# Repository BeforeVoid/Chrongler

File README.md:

# Chrongler

eurorack open-source module based on forestcover Benjolin with few mods.
+ Rungler clock input.
+ Band Pass output.
+ High Pass output.

Strictly for non-commercial use.

CC-By-NC 4.0, 2026.

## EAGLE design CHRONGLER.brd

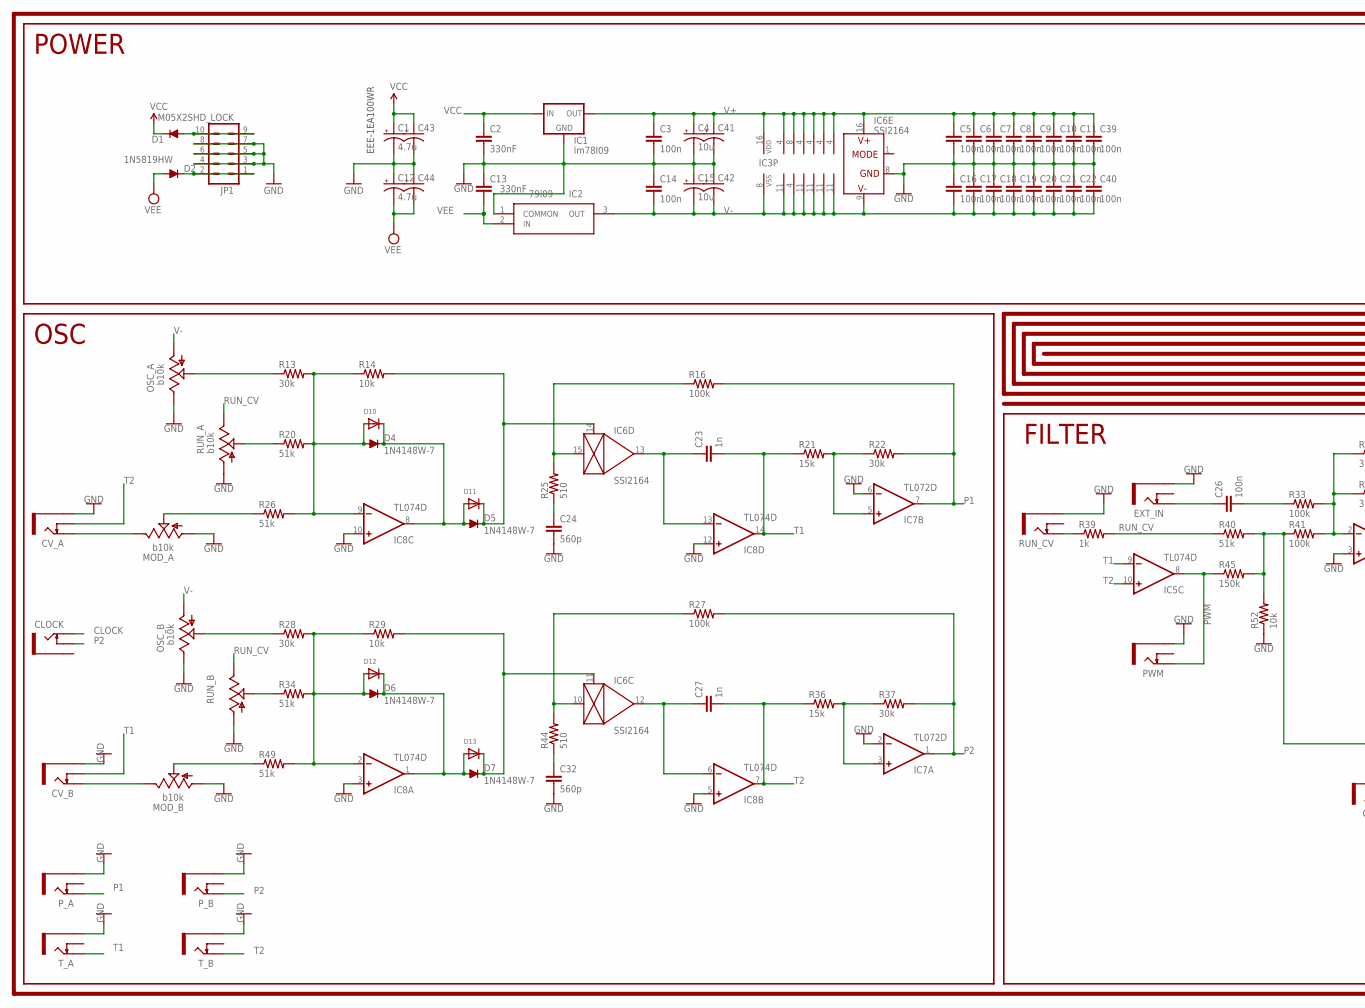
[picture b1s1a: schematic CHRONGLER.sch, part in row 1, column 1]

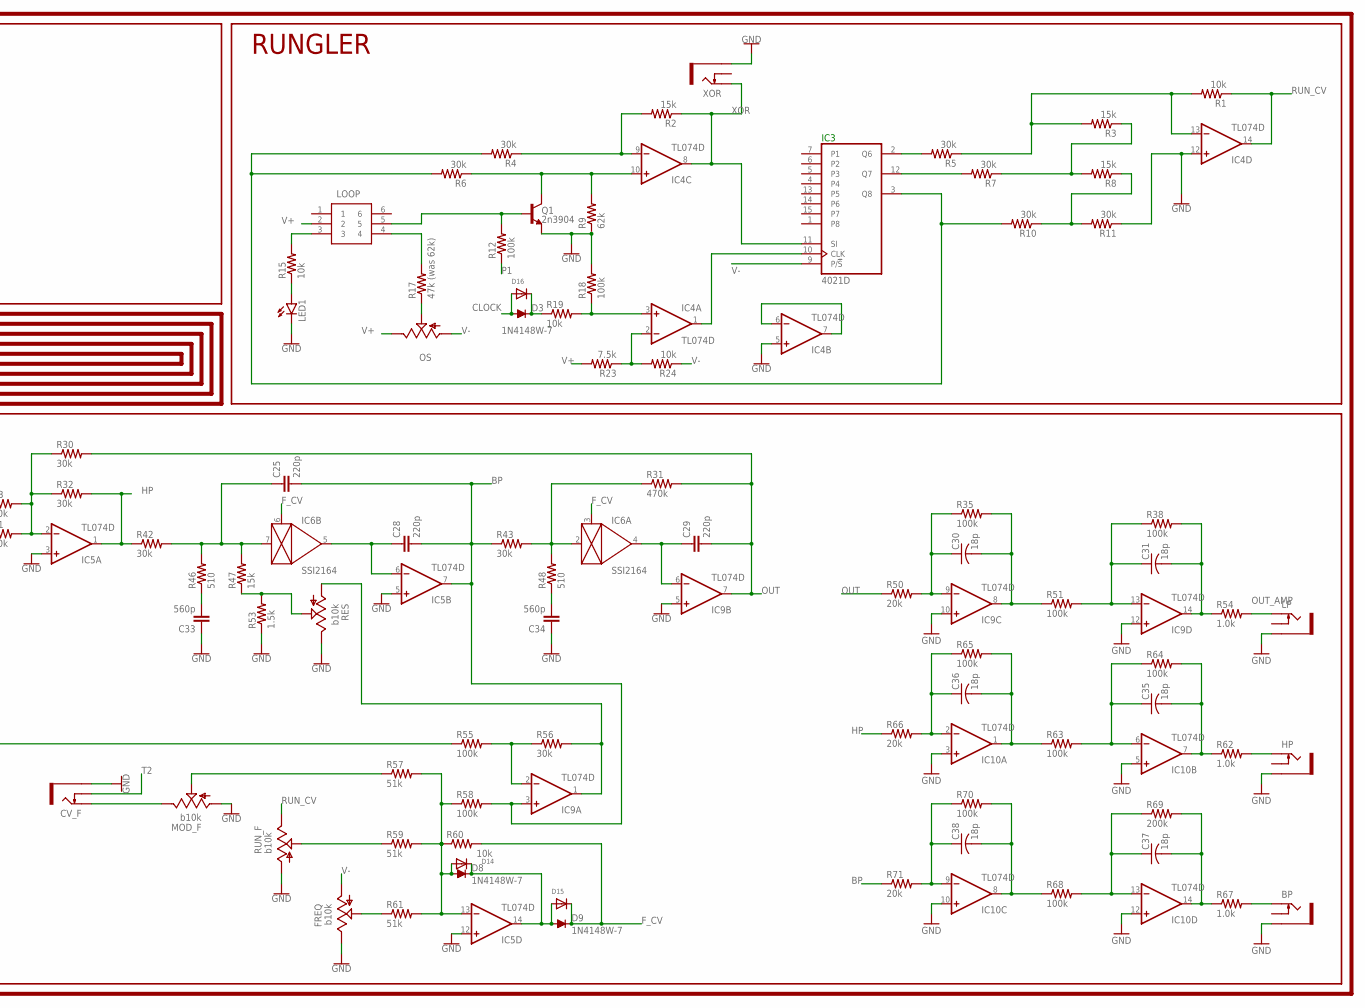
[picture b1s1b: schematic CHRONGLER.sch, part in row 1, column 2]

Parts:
BP: THONKICONNNEW; WQP-PJ301M-12_JACK
C1, C12: 4.7u; PANASONIC_C
C2, C13: 330nF; C1206
C3, C14: 100n; C1206
C4, C15: 10u; PANASONIC_C
C5, C6, C7, C8, C9, C10, C11, C16, C17, C18, C19, C20, C21, C22, C26, C39, C40: 100n; C0603
C23, C27: 1n; C0603
C24, C32, C33, C34: 560p; C0603
C25, C28, C29: 220p; C0603
C30, C31, C35, C36, C37, C38: 18p; C0603
C41, C42, C43, C44: CPOL-USE2.5-6; E2,5-6
CLOCK: THONKICONNNEW; WQP-PJ301M-12_JACK
CV_A: THONKICONNNEW; WQP-PJ301M-12_JACK
CV_B: THONKICONNNEW; WQP-PJ301M-12_JACK
CV_F: THONKICONNNEW; WQP-PJ301M-12_JACK
D1, D2: 1N5819HW; SOD123
D3, D4, D5, D6, D7, D8, D9: 1N4148W-7; SOD123
D10, D11, D12, D13, D14, D15, D16: DIODESOD-323F; SOD-323F
EXT_IN: THONKICONNNEW; WQP-PJ301M-12_JACK
FREQ: b10k; 9MM_SNAP-IN_POT
HP: THONKICONNNEW; WQP-PJ301M-12_JACK
IC1: lm78l09; SOT89
IC2: 79l09; SOT-89-3
IC3: 4021D; SO16
IC4, IC5, IC8, IC9, IC10: TL074D; SO14
IC6: SSI2164; SOIC16N
IC7: TL072D; SO08
JP1: M05X2SHD_LOCK; 2X5-SHROUDED_LOCK
LED1: LEDLD260; LD260
LOOP: MHPS2266; DIPS450W80P200L600H1050Q6N
LP: THONKICONNNEW; WQP-PJ301M-12_JACK
MOD_A: b10k; 9MM_SNAP-IN_POT
MOD_B: b10k; 9MM_SNAP-IN_POT
MOD_F: b10k; 9MM_SNAP-IN_POT
OS: 9MM_SNAP-IN_POT_; 9MM_SNAP-IN_POT
OSC_A: b10k; 9MM_SNAP-IN_POT
OSC_B: b10k; 9MM_SNAP-IN_POT
PWM: THONKICONNNEW; WQP-PJ301M-12_JACK
P_A: THONKICONNNEW; WQP-PJ301M-12_JACK
P_B: THONKICONNNEW; WQP-PJ301M-12_JACK
Q1: 2n3904; SOT23-3
R1, R14, R15, R19, R24, R29, R52, R60: 10k; R0603
R2, R3, R8, R21, R36, R47: 15k; R0603
R4, R5, R6, R7, R10, R11, R13, R22, R28, R30, R32, R37, R42, R43, R56: 30k; R0603
R9: 62k; R0603
R12, R16, R18, R27, R33, R35, R38, R41, R51, R55, R58, R63, R64, R65, R68, R70: 100k; R0603
R17: 47k (was 62k); R0603
R20, R26, R34, R40, R49, R57, R59, R61: 51k; R0603
R23: 7.5k; R0603
R25, R44, R46, R48: 510; R0603
R31: 470k; R0603
R39: 1k; R0603
R45: 150k; R0603
R50, R66, R71: 20k; R0603
R53: 1.5k; R0603
R54, R62, R67: 1.0k; R0603
R69: 200k; R0603
RES: b10k; 9MM_SNAP-IN_POT
RUN_A: b10k; 9MM_SNAP-IN_POT
RUN_B: 9MM_SNAP-IN_POT_; 9MM_SNAP-IN_POT
RUN_CV: THONKICONNNEW; WQP-PJ301M-12_JACK
RUN_F: b10k; 9MM_SNAP-IN_POT
T_A: THONKICONNNEW; WQP-PJ301M-12_JACK
T_B: THONKICONNNEW; WQP-PJ301M-12_JACK
XOR: THONKICONNNEW; WQP-PJ301M-12_JACK

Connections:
BP: C25.2, C28.2, IC5.7 (OUT), IC9.3 (+IN), R43.1, R58.2, R71.1
CLOCK: CLOCK.P$1_TIP (TIP), D3.A, D16.A
F_CV: D9.C, D15.C, IC6.3 (CTRL), IC6.6 (CTRL), R60.2
GND: BP.P$3_SLEEVE (SLEEVE), C1.-, C2.2, C3.2, C4.-, C5.2, C6.2, C7.2, C8.2, C9.2, C10.2, C11.2, C12.+, C13.1, C14.1, C15.+, C16.1, C17.1, C18.1, C19.1, C20.1, C21.1, C22.1, C24.2, C32.2, C33.1, C34.1, C39.2, C40.1, C41.-, C42.+, C43.-, C44.+, CV_A.P$3_SLEEVE (SLEEVE), CV_B.P$3_SLEEVE (SLEEVE), CV_F.P$3_SLEEVE (SLEEVE), EXT_IN.P$3_SLEEVE (SLEEVE), FREQ.3 (E), HP.P$3_SLEEVE (SLEEVE), IC1.2 (GND), IC1.2@1 (GND), IC2.1 (COMMON), IC4.5 (+IN), IC4.12 (+IN), IC5.3 (+IN), IC5.5 (+IN), IC5.12 (+IN), IC6.8 (GND), IC7.2 (-IN), IC7.6 (-IN), IC8.3 (+IN), IC8.5 (+IN), IC8.10 (+IN), IC8.12 (+IN), IC9.5 (+IN), IC9.10 (+IN), IC9.12 (+IN), IC10.3 (+IN), IC10.5 (+IN), IC10.10 (+IN), IC10.12 (+IN), JP1.3, JP1.4, JP1.5, JP1.6, JP1.7, JP1.8, LED1.K (C), LP.P$3_SLEEVE (SLEEVE), MOD_A.1 (A), MOD_B.1 (A), MOD_F.1 (A), OSC_A.3 (E), OSC_B.3 (E), PWM.P$3_SLEEVE (SLEEVE), P_A.P$3_SLEEVE (SLEEVE), P_B.P$3_SLEEVE (SLEEVE), Q1.2 (E), R9.1, R11.1, R18.2, R52.1, R53.1, RES.3 (E), RUN_A.1 (A), RUN_B.1 (A), RUN_CV.P$3_SLEEVE (SLEEVE), RUN_F.1 (A), T_A.P$3_SLEEVE (SLEEVE), T_B.P$3_SLEEVE (SLEEVE), XOR.P$3_SLEEVE (SLEEVE)
HP: IC5.1 (OUT), R32.2, R42.1, R66.1
unnamed: CV_A.P$1_TIP (TIP), MOD_A.3 (E)
unnamed: CV_B.P$1_TIP (TIP), MOD_B.3 (E)
unnamed: MOD_A.2 (S), R26.1
unnamed: MOD_B.2 (S), R49.1
unnamed: D4.A, D10.A, IC8.9 (-IN), R13.2, R14.1, R20.2, R26.2
unnamed: D2.C, JP1.1, JP1.2
unnamed: D6.A, D12.A, IC8.2 (-IN), R28.2, R29.1, R34.2, R49.2
unnamed: R34.1, RUN_B.2 (S)
unnamed: OSC_B.2 (S), R28.1
unnamed: OSC_A.2 (S), R13.1
unnamed: R20.1, RUN_A.2 (S)
unnamed: D4.C, D5.A, D10.C, D11.A, IC8.8 (OUT)
unnamed: D7.C, D13.C, IC6.11 (CTRL), R29.2
unnamed: D6.C, D7.A, D12.C, D13.A, IC8.1 (OUT)
unnamed: D5.C, D11.C, IC6.14 (CTRL), R14.2
unnamed: FREQ.2 (S), R61.1
unnamed: C31.2, IC9.14 (OUT), R38.2, R54.1
unnamed: C32.1, R44.1
unnamed: IC6.10 (IN), R27.1, R44.2
unnamed: D1.A, JP1.9, JP1.10
unnamed: IC6.15 (IN), R16.1, R25.2
unnamed: C24.1, R25.1
unnamed: C27.1, IC6.12 (OUT), IC8.6 (-IN)
unnamed: C23.1, IC6.13 (OUT), IC8.13 (-IN)
unnamed: IC7.3 (+IN), R36.2, R37.1
unnamed: IC7.5 (+IN), R21.2, R22.1
unnamed: LOOP.4, R17.2
unnamed: OS.2 (S), R17.1
unnamed: LOOP.5, Q1.1 (B), R12.2
unnamed: IC4.10 (+IN), Q1.3 (C), R6.1, R9.2
unnamed: IC4.9 (-IN), R2.2, R4.1
unnamed: IC3.2 (Q6), R5.2
unnamed: IC3.12 (Q7), R7.2
unnamed: IC3.3 (Q8), R4.2, R6.2, R10.2
unnamed: R3.1, R7.1, R8.2
unnamed: R8.1, R10.1, R11.2
unnamed: IC4.13 (-IN), R1.2, R3.2, R5.1
unnamed: R40.2, R41.1, R45.2, R52.2, R55.1
unnamed: C26.1, EXT_IN.P$1_TIP (TIP)
unnamed: C26.2, R33.1
unnamed: IC5.2 (-IN), R30.1, R32.1, R33.2, R41.2
unnamed: LED1.A, R15.1
unnamed: IC9.2 (-IN), R55.2, R56.1
unnamed: R47.1, R53.2, RES.2 (S)
unnamed: C33.2, R46.1
unnamed: C25.1, IC6.7 (IN), R42.2, R46.2, R47.2
unnamed: C28.1, IC5.6 (-IN), IC6.5 (OUT)
unnamed: IC4.6 (-IN), IC4.7 (OUT)
unnamed: D8.A, D14.A, IC5.13 (-IN), R57.2, R58.1, R59.2, R60.1, R61.2
unnamed: C34.2, R48.1
unnamed: IC6.2 (IN), R31.1, R43.2, R48.2
unnamed: C29.1, IC6.4 (OUT), IC9.6 (-IN)
unnamed: IC9.1 (OUT), R56.2, RES.1 (A)
unnamed: D8.C, D9.A, D14.C, D15.A, IC5.14 (OUT)
unnamed: IC4.3 (+IN), R18.1, R19.2
unnamed: R59.1, RUN_F.2 (S)
unnamed: CV_F.P$1_TIP (TIP), MOD_F.3 (E)
unnamed: MOD_F.2 (S), R57.1
unnamed: D3.C, D16.C, R19.1
unnamed: C30.1, IC9.9 (-IN), R35.1, R50.2
unnamed: C31.1, IC9.13 (-IN), R38.1, R51.2
unnamed: C30.2, IC9.8 (OUT), R35.2, R51.1
unnamed: IC4.2 (-IN), R23.1, R24.2
unnamed: IC3.10 (CLK), IC4.1 (OUT)
unnamed: R39.1, RUN_CV.P$1_TIP (TIP)
unnamed: LOOP.3, R15.2
unnamed: C35.1, IC10.6 (-IN), R63.2, R64.1
unnamed: C35.2, IC10.7 (OUT), R62.1, R64.2
unnamed: C36.1, IC10.2 (-IN), R65.1, R66.2
unnamed: C36.2, IC10.1 (OUT), R63.1, R65.2
unnamed: C37.1, IC10.13 (-IN), R68.2, R69.1
unnamed: C37.2, IC10.14 (OUT), R67.1, R69.2
unnamed: C38.1, IC10.9 (-IN), R70.1, R71.2
unnamed: C38.2, IC10.8 (OUT), R68.1, R70.2
unnamed: HP.P$1_TIP (TIP), R62.2
unnamed: BP.P$1_TIP (TIP), R67.2
OUT: C29.2, IC9.7 (OUT), R30.2, R31.2, R50.1
OUT_AMP: LP.P$1_TIP (TIP), R54.2
P1: IC7.7 (OUT), P_A.P$1_TIP (TIP), R12.1, R16.2, R22.2
P2: CLOCK.P$2_SWITCH (SWITCH), IC7.1 (OUT), P_B.P$1_TIP (TIP), R27.2, R37.2
PWM: IC5.8 (OUT), PWM.P$1_TIP (TIP), R45.1
RUN_CV: IC4.14 (OUT), R1.1, R39.2, R40.1, RUN_A.3 (E), RUN_B.3 (E), RUN_F.3 (E)
T1: C23.2, CV_B.P$2_SWITCH (SWITCH), IC5.9 (-IN), IC8.14 (OUT), R21.1, T_A.P$1_TIP (TIP)
T2: C27.2, CV_A.P$2_SWITCH (SWITCH), CV_F.P$2_SWITCH (SWITCH), IC5.10 (+IN), IC8.7 (OUT), R36.1, T_B.P$1_TIP (TIP)
V+: C3.1, C4.+, C5.1, C6.1, C7.1, C8.1, C9.1, C10.1, C11.1, C39.1, C41.+, IC1.1 (OUT), IC3.16 (VDD), IC4.4 (V+), IC5.4 (V+), IC6.16 (V+), IC7.8 (V+), IC8.4 (V+), IC9.4 (V+), IC10.4 (V+), LOOP.2, OS.3 (E), R23.2
V-: C14.2, C15.-, C16.2, C17.2, C18.2, C19.2, C20.2, C21.2, C22.2, C40.2, C42.-, FREQ.1 (A), IC2.3 (OUT), IC3.8 (VSS), IC3.9 (P/!S), IC4.11 (V-), IC5.11 (V-), IC6.9 (V-), IC7.4 (V-), IC8.11 (V-), IC9.11 (V-), IC10.11 (V-), OS.1 (A), OSC_A.1 (A), OSC_B.1 (A), R24.1
VCC: C1.+, C2.1, C43.+, D1.C, IC1.3 (IN)
VEE: C12.-, C13.2, C44.-, D2.A, IC2.2 (IN)
XOR: IC3.11 (SI), IC4.8 (OUT), R2.1, XOR.P$1_TIP (TIP)

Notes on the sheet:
EEE-1EA100WR
POWER
OSC
FILTER
RUNGLER

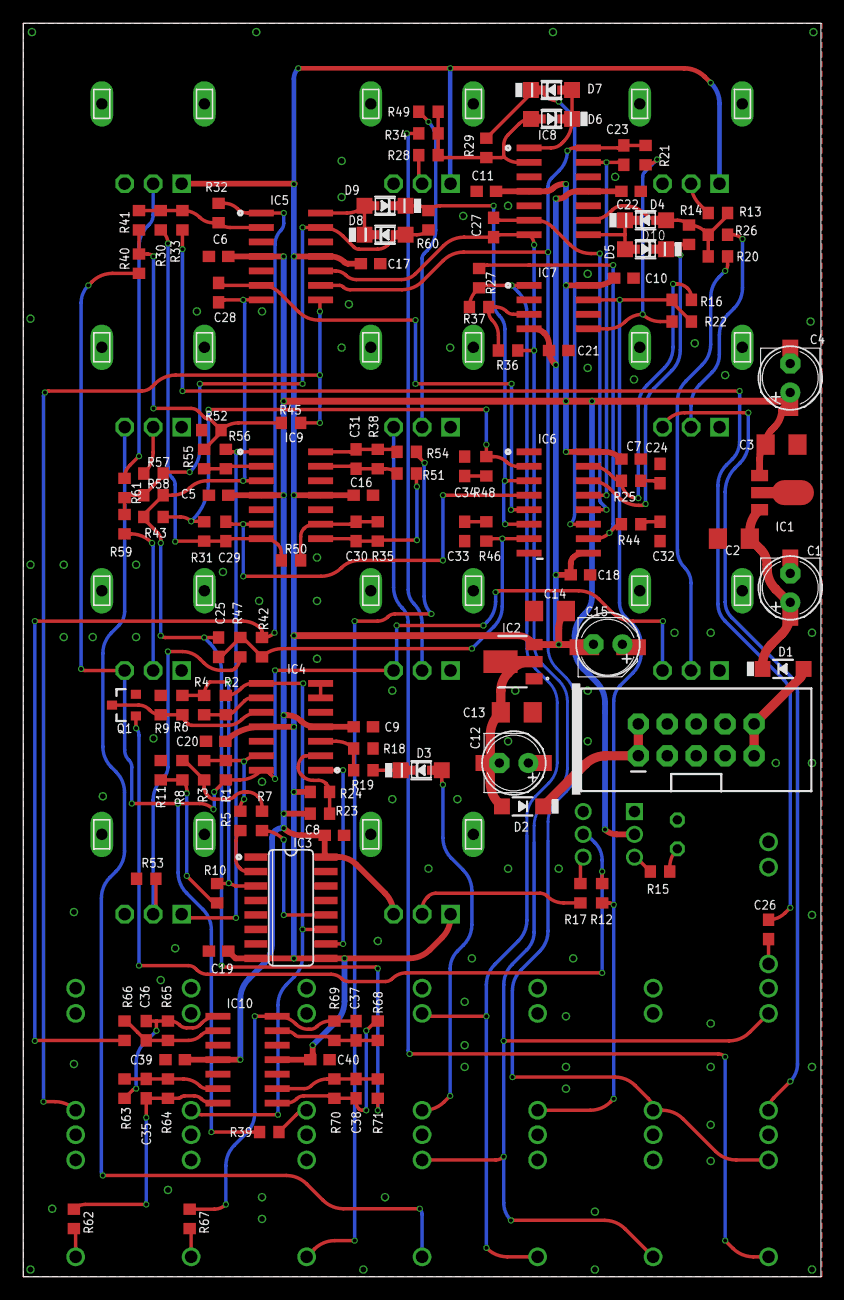
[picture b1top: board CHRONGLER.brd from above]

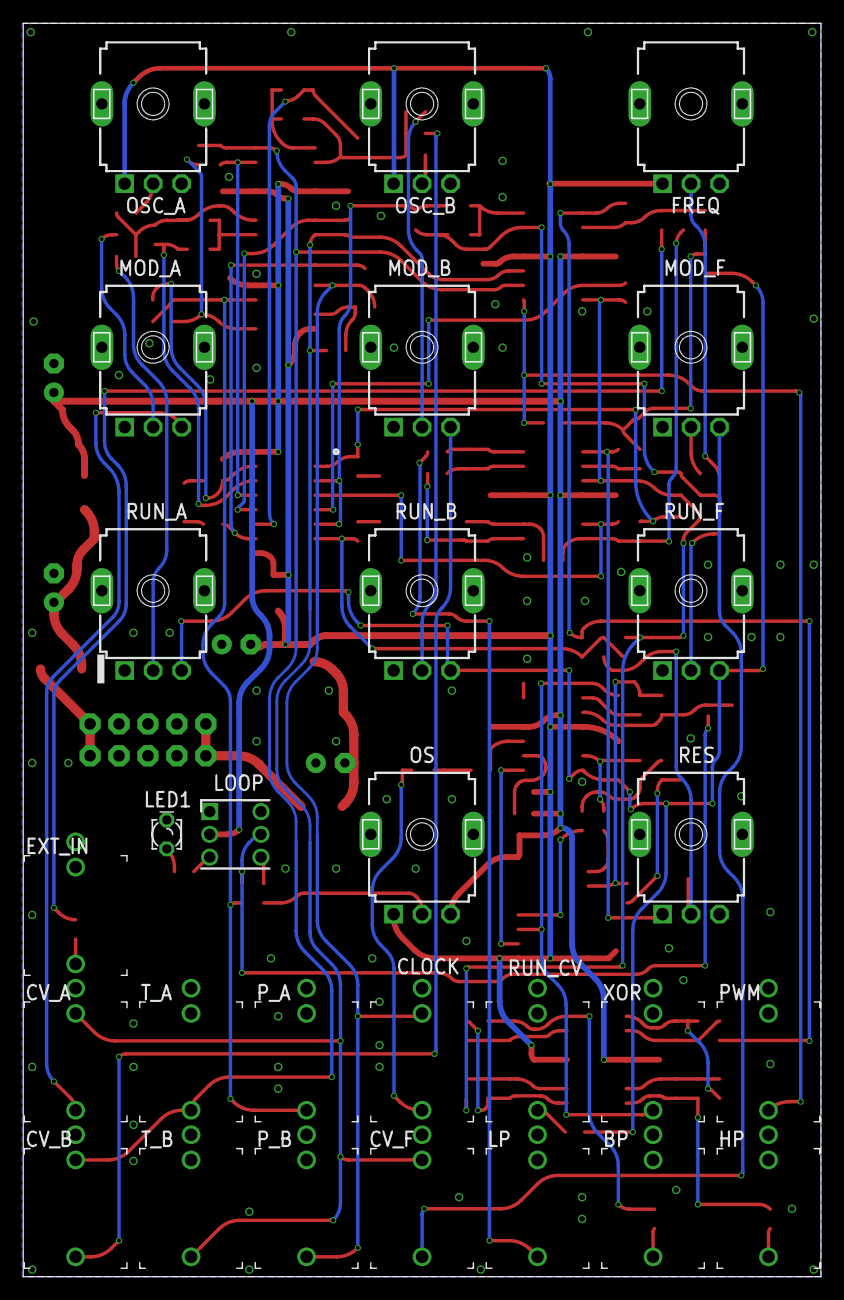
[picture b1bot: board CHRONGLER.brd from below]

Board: 2 copper layers, 70.0 x 110.0 mm, 171 parts (28 on the bottom side), 94 nets.

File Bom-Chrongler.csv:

"Qty";"Value";"Device";"Package";"Parts";"Description";"";
"4";"";"CPOL-USE2.5-6";"E2,5-6";"C41, C42, C43, C44";"POLARIZED CAPACITOR, American symbol";"";
"7";"";"DIODESOD-323F";"SOD-323F";"D10, D11, D12, D13, D14, D15, D16";"Diode";"";
"1";"";"LEDLD260";"LD260";"LED1";"LED";"";
"3";"1.0k";"R-US_R0603";"R0603";"R54, R62, R67";"RESISTOR, American symbol";"";
"1";"1.5k";"R-US_R0603";"R0603";"R53";"RESISTOR, American symbol";"";
"16";"100k";"R-US_R0603";"R0603";"R12, R16, R18, R27, R33, R35, R38, R41, R51, R55, R58, R63, R64, R65, R68, R70";"RESISTOR, American symbol";"";
"17";"100n";"C-EUC0603";"C0603";"C5, C6, C7, C8, C9, C10, C11, C16, C17, C18, C19, C20, C21, C22, C26, C39, C40";"CAPACITOR, European symbol";"";
"2";"100n";"C-EUC1206";"C1206";"C3, C14";"CAPACITOR, European symbol";"";
"8";"10k";"R-US_R0603";"R0603";"R1, R14, R15, R19, R24, R29, R52, R60";"RESISTOR, American symbol";"";
"2";"10u";"CPOL-USC";"PANASONIC_C";"C4, C15";"POLARIZED CAPACITOR, American symbol";"";
"1";"150k";"R-US_R0603";"R0603";"R45";"RESISTOR, American symbol";"";
"6";"15k";"R-US_R0603";"R0603";"R2, R3, R8, R21, R36, R47";"RESISTOR, American symbol";"";
"6";"18p";"C-USC0603";"C0603";"C30, C31, C35, C36, C37, C38";"CAPACITOR, American symbol";"";
"7";"1N4148W-7";"1N4148W-7";"SOD123";"D3, D4, D5, D6, D7, D8, D9";"DIODE";"";
"2";"1N5819HW";"DIODE-SOD123";"SOD123";"D1, D2";"DIODE";"";
"1";"1k";"R-US_R0603";"R0603";"R39";"RESISTOR, American symbol";"";
"2";"1n";"C-EUC0603";"C0603";"C23, C27";"CAPACITOR, European symbol";"";
"1";"200k";"R-US_R0603";"R0603";"R69";"RESISTOR, American symbol";"";
"3";"20k";"R-US_R0603";"R0603";"R50, R66, R71";"RESISTOR, American symbol";"";
"3";"220p";"C-EUC0603";"C0603";"C25, C28, C29";"CAPACITOR, European symbol";"";
"1";"2n3904";"TRANS_NPN-MMBT2222AL";"SOT23-3";"Q1";"NPN transistor";"";
"15";"30k";"R-US_R0603";"R0603";"R4, R5, R6, R7, R10, R11, R13, R22, R28, R30, R32, R37, R42, R43, R56";"RESISTOR, American symbol";"";
"2";"330nF";"C-EUC1206";"C1206";"C2, C13";"CAPACITOR, European symbol";"";
"2";"4.7u";"CPOL-USC";"PANASONIC_C";"C1, C12";"POLARIZED CAPACITOR, American symbol";"";
"1";"4021D";"4021D";"SO16";"IC3";"8-bit static SHIFT REGISTER";"";
"1";"470k";"R-US_R0603";"R0603";"R31";"RESISTOR, American symbol";"";
"1";"47k (was 62k)";"R-US_R0603";"R0603";"R17";"RESISTOR, American symbol";"";
"4";"510";"R-US_R0603";"R0603";"R25, R44, R46, R48";"RESISTOR, American symbol";"";
"8";"51k";"R-US_R0603";"R0603";"R20, R26, R34, R40, R49, R57, R59, R61";"RESISTOR, American symbol";"";
"4";"560p";"C-EUC0603";"C0603";"C24, C32, C33, C34";"CAPACITOR, European symbol";"";
"1";"62k";"R-US_R0603";"R0603";"R9";"RESISTOR, American symbol";"";
"1";"7.5k";"R-US_R0603";"R0603";"R23";"RESISTOR, American symbol";"";
"1";"79l09";"NJM79L05UA-TE1";"SOT-89-3";"IC2";"Linear Voltage Regulators -5V .1A 3 Terminal";"";
"1";"M05X2SHD_LOCK";"M05X2SHD_LOCK";"2X5-SHROUDED_LOCK";"JP1";"Header 5x2";"";
"1";"MHPS2266";"MHPS2266";"DIPS450W80P200L600H1050Q6N";"LOOP";"APEM - MHPS2266 - \u94A5\u5319\u5F00\u5173, DPDT, 100mA, 30VDC, PCB";"";
"1";"SSI2164";"SSM2164S";"SOIC16N";"IC6";"";"";
"15";"THONKICONNNEW";"THONKICONNNEW";"WQP-PJ301M-12_JACK";"BP, CLOCK, CV_A, CV_B, CV_F, EXT_IN, HP, LP, PWM, P_A, P_B, RUN_CV, T_A, T_B, XOR";"3.5mm socket for Eurorack modular synths";"";
"1";"TL072D";"TL072D";"SO08";"IC7";"OP AMP";"";
"5";"TL074D";"TL074D";"SO14";"IC4, IC5, IC8, IC9, IC10";"OP AMP";"";
"11";"b10k";"9MM_SNAP-IN_POT_";"9MM_SNAP-IN_POT";"FREQ, MOD_A, MOD_B, MOD_F, OS, OSC_A, OSC_B, RES, RUN_A, RUN_B, RUN_F";"9mm vertical snap-in pot, Alpha / Panasonic style";"";
"1";"lm78l09";"78LXX-SOT89";"SOT89";"IC1";"VOLTAGE REGULATOR";"";

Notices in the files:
parts and their libraries:
SparkFun-DiscreteSemi: Licensing: Creative Commons ShareAlike 4.0 International - https://creativecommons.org/licenses/by-sa/4.0
